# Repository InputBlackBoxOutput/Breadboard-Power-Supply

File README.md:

# Breadboard Power Supply

A convenient power supply to provide power while building and testing analog/digital circuits on a breadboard

## Features
* Snaps right onto a breadboard
* Ships with 2 variants SMD and THT for choice of components
* Input power can be derived from a 12V SMPS via barrel jack or 5V via USB cable
* Switches to switch the output voltages on/off 
* Provides variable voltage 

## Technical specification
* *Output voltages:* Fixed: 5 ± 0.150V and 3.3 ± 0.099V and Variable: 1.25V to ≈Vsupply 
* *Output currents:* 1.1A max for each voltage when connected to a 12V 2A SMPS and 500 mA total when connected to USB

### Caution: Do not connect current hungry components when input power is provided via USB 

## 3D Render
| SMD variant | THT variant |
|--|--|
|||

### Made with lots of ⏱️, 📚 and ☕ by InputBlackBoxOutput

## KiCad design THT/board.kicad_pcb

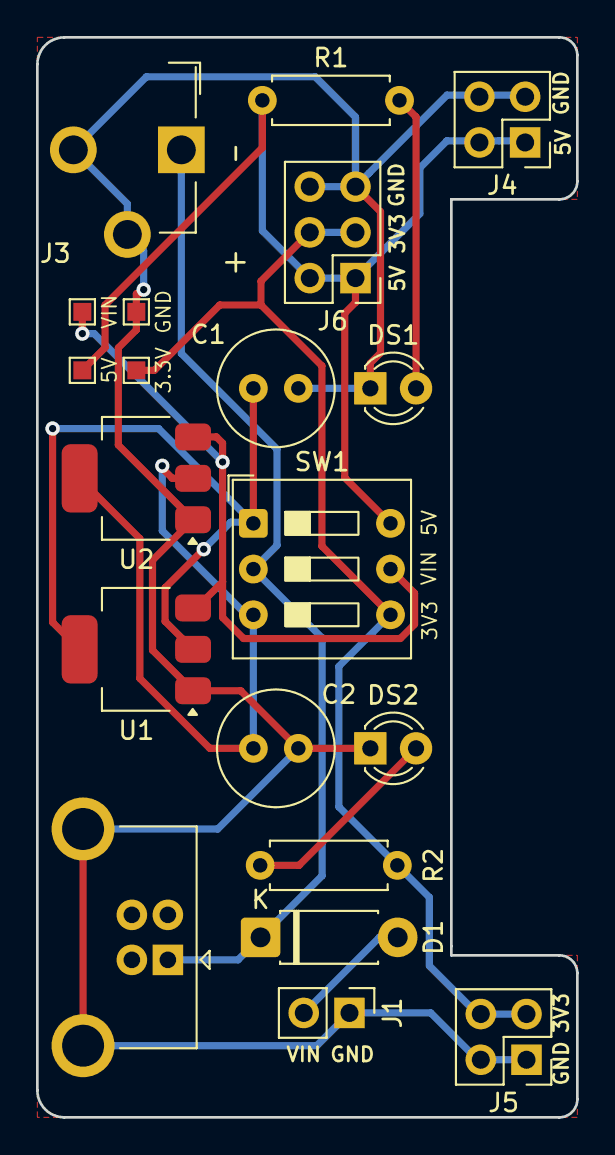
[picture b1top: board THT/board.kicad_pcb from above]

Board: 2 copper layers, 30.0 x 60.0 mm, 20 parts (0 on the bottom side), 10 nets.

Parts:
3.3V, 5V: TestPoint; TestPoint_Pad_1.0x1.0mm
C1, C2: 22uF; C_Radial_D6.3mm_H11.0mm_P2.50mm
D1: 1N4007; D_DO-41_SOD81_P7.62mm_Horizontal
DS1, DS2: LED; LED_D3.0mm
GND: TestPoint; TestPoint_Pad_1.0x1.0mm
J1: 9V Battery; PinHeader_1x02_P2.54mm_Vertical
J2: USB_B; USB_B_OST_USB-B1HSxx_Horizontal
J3: Barrel_Jack_Switch; BarrelJack_CUI_PJ-102AH_Horizontal
J4: 1; PinHeader_2x02_P2.54mm_Vertical
J5: 2; PinHeader_2x02_P2.54mm_Vertical
J6: 3; PinHeader_2x03_P2.54mm_Vertical
R1: 2.2k; R_Axial_DIN0207_L6.3mm_D2.5mm_P7.62mm_Horizontal
R2: 1.5k; R_Axial_DIN0207_L6.3mm_D2.5mm_P7.62mm_Horizontal
SW1: SW_DIP_x03; SW_DIP_SPSTx03_Slide_9.78x9.8mm_W7.62mm_P2.54mm
U1: AMS1117-5.0; SOT-223-3_TabPin2
U2: AMS1117-3.3; SOT-223-3_TabPin2
VIN: TestPoint; TestPoint_Pad_1.0x1.0mm

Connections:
+3.3V: 3.3V.1 (1_1), J5.3, J5.4, J6.3, J6.4, R2.1, SW1.4
+5V: 5V.1 (1_1), J4.1, J4.2, J6.1, J6.2, R1.1, SW1.6
/3.3V: C2.1, SW1.3, U2.2 (VO)
/5V: C1.1, SW1.1, U1.2 (VO)
/VIN: SW1.5, U1.3 (VI), U2.3 (VI), VIN.1 (1_1)
GND: C1.2, C2.2, DS1.1 (K), DS2.1 (K), GND.1 (1_1), J1.1, J2.5 (Shield), J3.2, J3.3, J4.3, J4.4, J5.1, J5.2, J6.5, J6.6, U1.1 (GND), U2.1 (GND)
unnamed: D1.2 (A), J1.2
unnamed: DS1.2 (A), R1.2
unnamed: DS2.2 (A), R2.2
VDC: D1.1 (K), J2.1 (VBUS), J3.1, SW1.2

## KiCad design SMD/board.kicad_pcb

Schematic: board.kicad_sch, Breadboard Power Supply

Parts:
C1: 0.1uF; C_1206_3216Metric_Pad1.33x1.80mm_HandSolder
C2: 1uF; C_1206_3216Metric_Pad1.33x1.80mm_HandSolder
C3, C4: 22uF; C_1206_3216Metric_Pad1.33x1.80mm_HandSolder
D1: SS22T3G; D_SMB
DS1, DS2, DS3: LED; LED_1206_3216Metric_Pad1.42x1.75mm_HandSolder
J1: 9V Battery; PinHeader_1x02_P2.54mm_Vertical_SMD_Pin1Left
J2: Barrel_Jack_Switch; BarrelJack_CUI_PJ-102AH_Horizontal
J3: USB_B; USB_B_OST_USB-B1HSxx_Horizontal
J4: 1; PinHeader_2x02_P2.54mm_Vertical
J5: 2; PinHeader_2x02_P2.54mm_Vertical
J6: Conn_02x04_Odd_Even; PinHeader_2x04_P2.54mm_Vertical_SMD
R1: 5k; Potentiometer_Bourns_3314G_Vertical
R2: 240R; R_0805_2012Metric_Pad1.20x1.40mm_HandSolder
R3: 2.2k; R_0805_2012Metric_Pad1.20x1.40mm_HandSolder
R4: 1k; R_0805_2012Metric_Pad1.20x1.40mm_HandSolder
R5: 820R; R_0805_2012Metric_Pad1.20x1.40mm_HandSolder
SW1: SW_DIP_x04; SW_DIP_SPSTx04_Slide_9.78x12.34mm_W8.61mm_P2.54mm
TP1, TP2, TP3, TP4, TP5: TestPoint; TestPoint_Pad_1.0x1.0mm
U1: LM317; SOT-223-3_TabPin2
U2: AMS1117-5.0; SOT-223-3_TabPin2
U3: AMS1117-3.3; SOT-223-3_TabPin2

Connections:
+3.3V: J5.3, J5.4, J6.3, J6.4, R4.1, SW1.6, TP4.1 (1_1)
+5V: J4.1, J4.2, J6.1, J6.2, R3.1, SW1.8, TP3.1 (1_1)
/3.3V: C4.1, SW1.3, U3.2 (VO)
/5V: C3.1, SW1.1, U2.2 (VO)
/V: J6.5, J6.6, R5.1, SW1.5, TP5.1 (1_1)
/VIN: C1.1, SW1.7, TP1.1 (1_1), U1.3 (VI), U2.3 (VI), U3.3 (VI)
/VOUT: C2.1, R2.1, SW1.4, U1.2 (VO)
GND: C1.2, C2.2, C3.2, C4.2, DS1.1 (K), DS2.1 (K), DS3.1 (K), J1.1, J2.2, J2.3, J3.4 (GND), J3.5 (Shield), J4.3, J4.4, J5.1, J5.2, J6.7, J6.8, R1.2, TP2.1 (1_1), U2.1 (GND), U3.1 (GND)
unnamed: D1.2 (A), J1.2
unnamed: DS1.2 (A), R3.2
unnamed: DS2.2 (A), R4.2
unnamed: DS3.2 (A), R5.2
unnamed: R1.1, R2.2, U1.1 (ADJ)
VDC: D1.1 (K), J2.1, J3.1 (VBUS), SW1.2

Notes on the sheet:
text sample 3
RED
-------------------------------------------- # Current limiting resistor R = (Vs - Vled)/Iled Vled-red = 2V typical R @ 5V = 2.2k Iled = 1.3 mA R @ 3.3V = 1.5k Iled = 1.3 mA R @ var = 820R Iled =10.9 mA (At Vs-max = 12V) --------------------------------------------
Use 2k pot if available
# Reverse voltage protection diode Imax = 2A Vrev-max = 20V Vf = 0.3V - 0.4V for ≈1A --------------------------------------------
Variable power supply
Output connectors
Input connectors
# Variable voltage supply Vout = 1.25 * (1+ (R2/R1)) Vout-max = Vin = 12V Substituting Vout = 12V and R1 = 240 ohm we get R2 ≈ 2 kohm --------------------------------------------
Test points
Design notes:
Power control switches
Check polarity
Voltage regulators
LED indicators
AMS-1117 voltage regulators features - Low dropout voltage - Both 5V and 3.3V variant available - Maximum current = 1.1 A

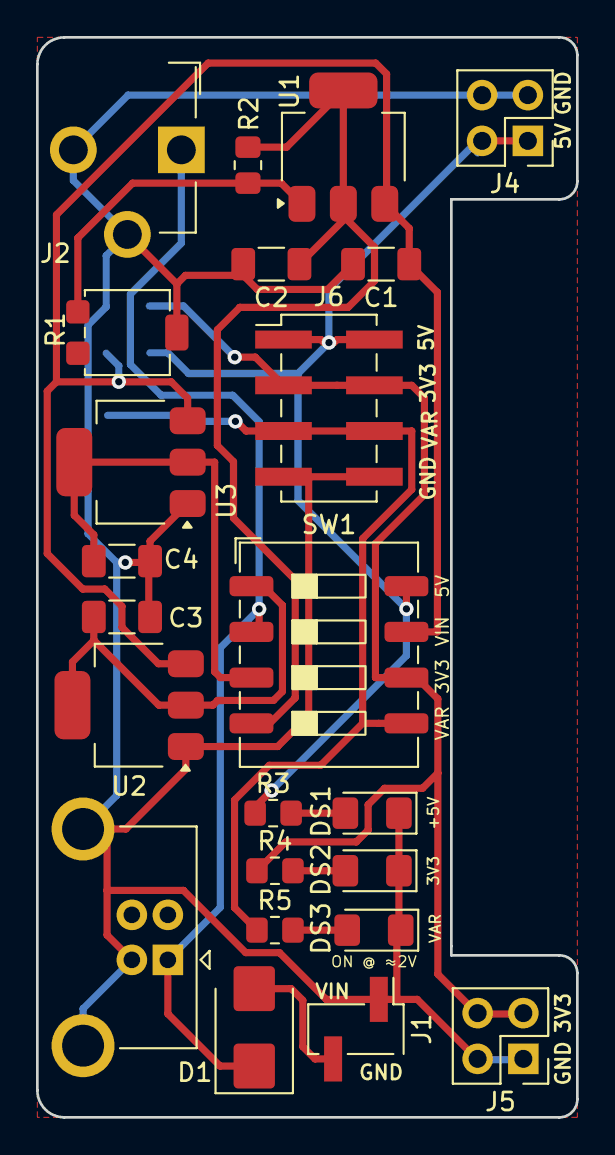
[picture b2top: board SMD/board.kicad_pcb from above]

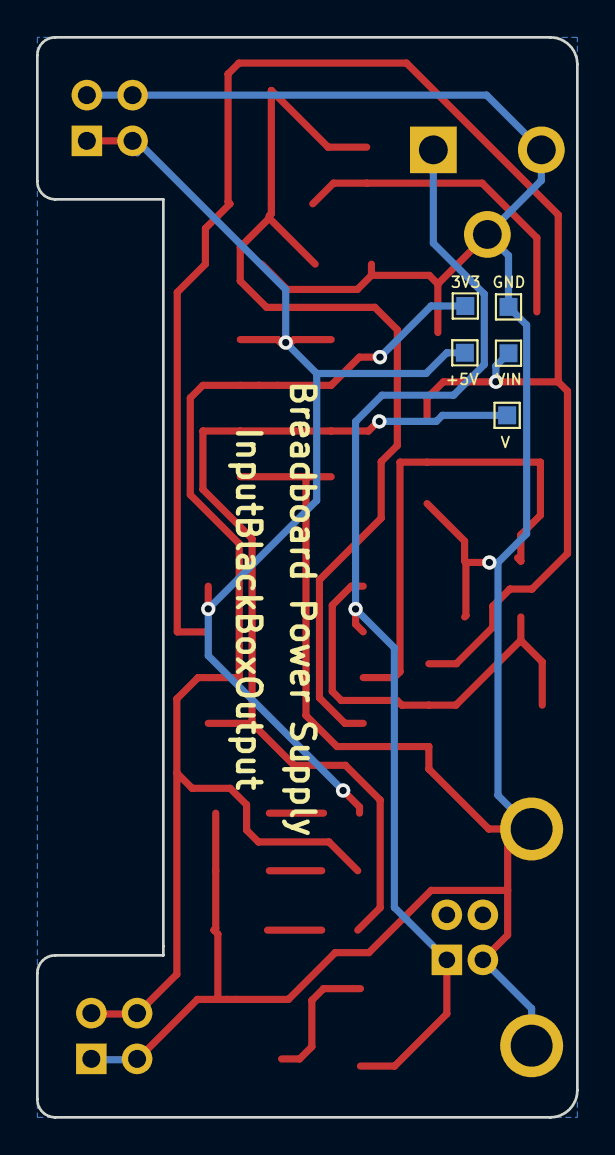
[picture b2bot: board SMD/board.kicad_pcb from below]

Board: 2 copper layers, 30.0 x 60.0 mm, 28 parts (5 on the bottom side), 14 nets.

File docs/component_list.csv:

Id,Designator,Package,Quantity,Designation
1,D1,D_SMB,1,SS22T3G
2,R1,Potentiometer_Bourns_3314G_Vertical,1,5k
3,U1,SOT-223,1,LM317_3PinPackage
4,SW1,SW_DIP_SPSTx04_Slide_9.78x12.34mm_W8.61mm_P2.54mm,1,SW_DIP_x04
5,R5,R_0805_2012Metric_Pad1.15x1.40mm_HandSolder,1,820R
6,R2,R_0805_2012Metric_Pad1.15x1.40mm_HandSolder,1,240R
7,J6,PinHeader_2x04_P2.54mm_Vertical_SMD,1,Conn_02x04_Odd_Even
8,"DS3,DS2,DS1",LED_1206_3216Metric_Pad1.42x1.75mm_HandSolder,3,LED
9,C2,C_1206_3216Metric_Pad1.42x1.75mm_HandSolder,1,1uF
10,C1,C_1206_3216Metric_Pad1.42x1.75mm_HandSolder,1,0.1uF
11,J5,PinHeader_2x02_P2.54mm_Vertical,1,2
12,J4,PinHeader_2x02_P2.54mm_Vertical,1,1
13,R4,R_0805_2012Metric_Pad1.15x1.40mm_HandSolder,1,1.5k
14,R3,R_0805_2012Metric_Pad1.15x1.40mm_HandSolder,1,2.2k
15,J1,PinHeader_1x02_P2.54mm_Vertical_SMD_Pin1Left,1,9V Battery
16,"C4,C3",C_1206_3216Metric_Pad1.42x1.75mm_HandSolder,2,22uF
17,J3,USB_B_OST_USB-B1HSxx_Horizontal,1,USB_B
18,J2,BarrelJack_CUI_PJ-102AH_Horizontal,1,Barrel_Jack_Switch
19,U3,SOT-223-3_TabPin2,1,AMS1117-3.3
20,U2,SOT-223-3_TabPin2,1,AMS1117-5.0

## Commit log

2020-11-13 Schematic and PCB design added
2020-11-13 Images and datasheets added
2020-11-13 Images added to README
2020-11-14 Gerber files and list of components added
2020-11-14 Markings improved
2020-11-24 Images changed
2020-12-08 Images resized
2020-12-15 Technical info added to README
2020-12-16 Minor changes to README
2021-06-07 3D models added to PCB
2021-06-07 Changed most footprints to SMD + Variable voltage
2021-06-07 README: Info update
2021-06-08 Protection diode changed + Datasheets
2021-06-08 README: Link and images of old variant added
2021-06-08 README: Info added
2021-06-12 Calculations added
2021-06-12 Gerber files and component list updated
2021-11-09 Minor changes
2022-07-03 Repository reorganized
2022-07-03 README: Render images not displaying fixed
2026-05-02 Restructure repository
2026-06-11 SMD Kicad 10
2026-06-11 THT Kicad 10
2026-06-14 README
